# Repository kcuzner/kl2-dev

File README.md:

# Kinetis KL2 Development Board
### Kevin Cuzner

## Objective

Create a development board for a bare-metal ARM Microcontroller with minimal
parts while allowing for maximum prototypability.

## Purpose

To learn from hard experience what exactly is needed to implement from the
ground up a platform using an ARM-based microcontroller

## Idea

The board will have the following:

 * The Freescale MKL26Z32VFM4 48Mhz ARM Cortex-M0+ microcontroller, 32QFN (5mm)
 * Any needed support componenets
 * A DIP-compatible footprint. The goal is to be near the size of a teensy.

The goals are as follows:

 * $10 price point
    * $2.72 for the uC
    * $5 board
    * $3 supporting components
        * Perhaps a USB port even
 * Easy to construct with sufficient SMD soldering skill
 * We will produce 3 of them
    * 1 practice, 2 assembled on camera

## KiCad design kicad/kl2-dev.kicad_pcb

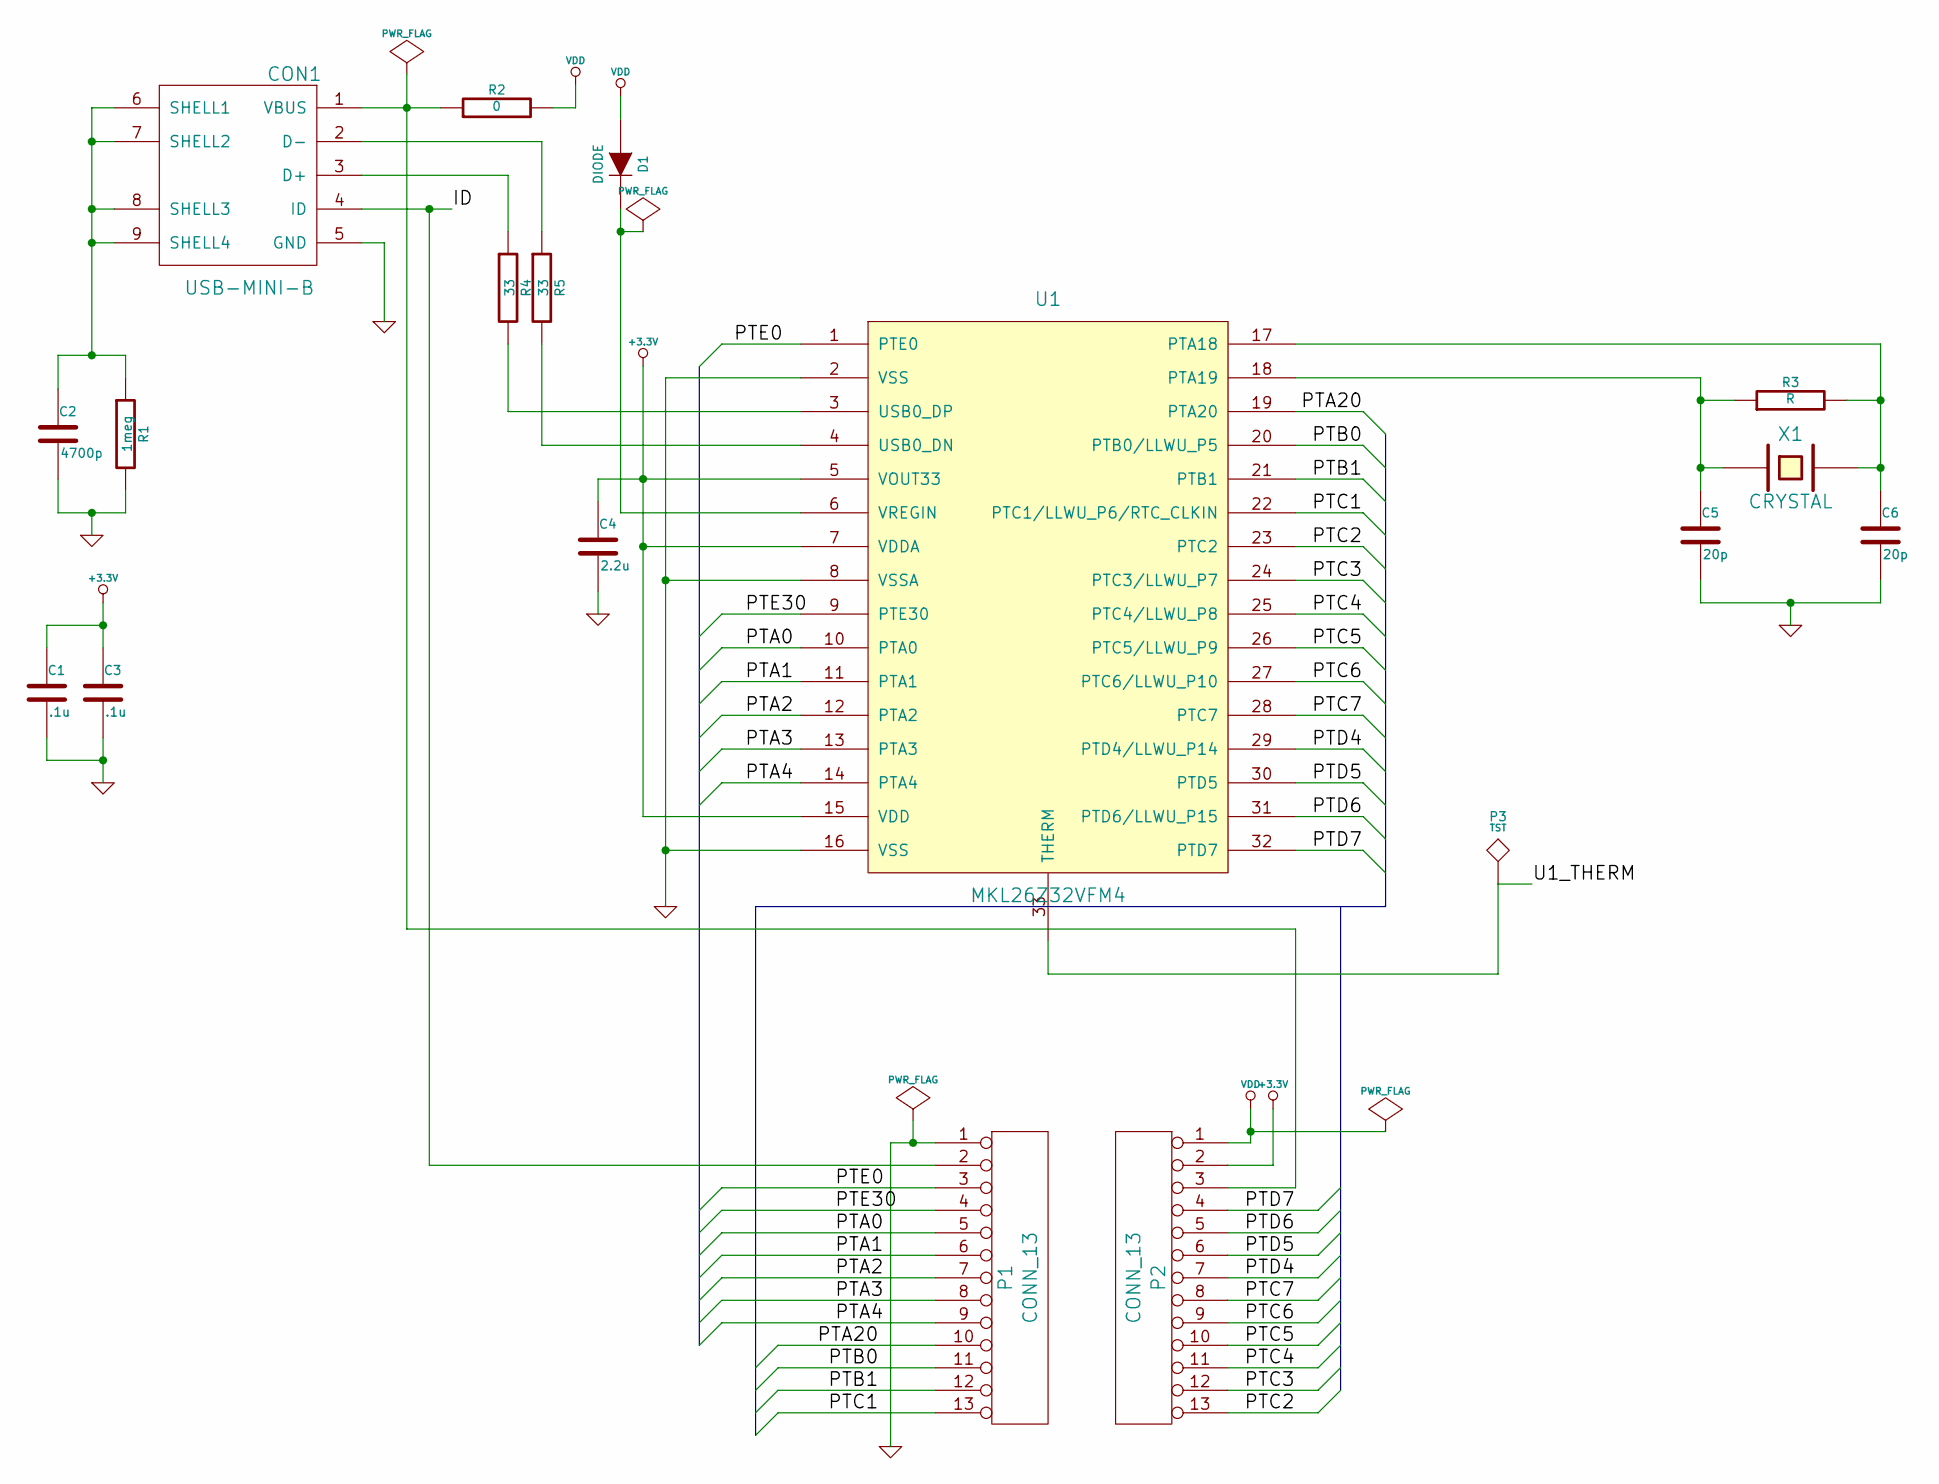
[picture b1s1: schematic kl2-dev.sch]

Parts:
C1, C3: .1u
C2: 4700p
C4: 2.2u
C5, C6: 20p
CON1: USB-MINI-B
D1: DIODE
P1, P2: CONN_13
P3: TST
R1: 1meg
R2: 0
R3: R
R4, R5: 33
U1: MKL26Z32VFM4
X1: CRYSTAL

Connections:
+3.3V: C1.1, C3.1, C4.1, P2.2, U1.5 (VOUT33), U1.7 (VDDA), U1.15 (VDD)
/ID: CON1.4 (ID), P1.2
/PTA0: P1.5, U1.10 (PTA0)
/PTA1: P1.6, U1.11 (PTA1)
/PTA2: P1.7, U1.12 (PTA2)
/PTA3: P1.8, U1.13 (PTA3)
/PTA4: P1.9, U1.14 (PTA4)
/PTA20: P1.10, U1.19 (PTA20)
/PTB0: P1.11, U1.20 (PTB0/LLWU_P5)
/PTB1: P1.12, U1.21 (PTB1)
/PTC1: P1.13, U1.22 (PTC1/LLWU_P6/RTC_CLKIN)
/PTC2: P2.13, U1.23 (PTC2)
/PTC3: P2.12, U1.24 (PTC3/LLWU_P7)
/PTC4: P2.11, U1.25 (PTC4/LLWU_P8)
/PTC5: P2.10, U1.26 (PTC5/LLWU_P9)
/PTC6: P2.9, U1.27 (PTC6/LLWU_P10)
/PTC7: P2.8, U1.28 (PTC7)
/PTD4: P2.7, U1.29 (PTD4/LLWU_P14)
/PTD5: P2.6, U1.30 (PTD5)
/PTD6: P2.5, U1.31 (PTD6/LLWU_P15)
/PTD7: P2.4, U1.32 (PTD7)
/PTE0: P1.3, U1.1 (PTE0)
/PTE30: P1.4, U1.9 (PTE30)
/U1_THERM: P3.1, U1.33 (THERM)
GND: C1.2, C2.2, C3.2, C4.2, C5.2, C6.2, CON1.5 (GND), P1.1, R1.2, U1.2 (VSS), U1.8 (VSSA), U1.16 (VSS)
unnamed: C5.1, R3.1, U1.18 (PTA19), X1.1
unnamed: C6.1, R3.2, U1.17 (PTA18), X1.2
unnamed: C2.1, CON1.6 (SHELL1), CON1.7 (SHELL2), CON1.8 (SHELL3), CON1.9 (SHELL4), R1.1
unnamed: D1.2 (K), U1.6 (VREGIN)
unnamed: R4.2, U1.3 (USB0_DP)
unnamed: CON1.3 (D+), R4.1
unnamed: R5.2, U1.4 (USB0_DN)
unnamed: CON1.2 (D-), R5.1
unnamed: CON1.1 (VBUS), P2.3, R2.1
VDD: D1.1 (A), P2.1, R2.2

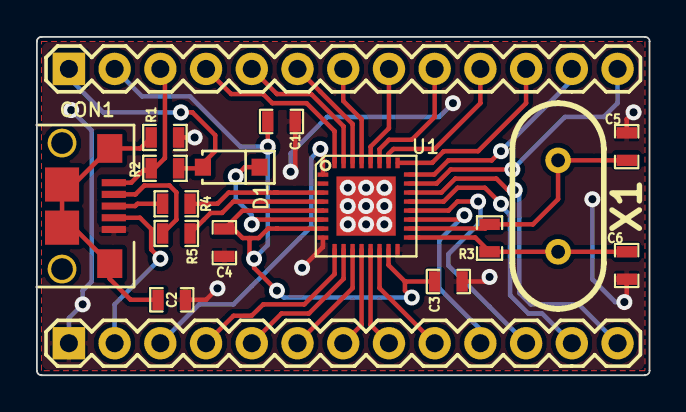
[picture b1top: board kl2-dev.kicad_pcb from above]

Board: 2 copper layers, 34.0 x 18.8 mm, 18 parts (1 on the bottom side), 35 nets.

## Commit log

2014-10-24 Created initial board with demonstration thermal pad
    We need pin 33 to be on its own special net because it shouldn't be
    connected. We also have not yet routed the flows.
2014-10-25 Finished routing all but gnd and thermal pad
2014-10-25 Added thermal pad and vias
2014-10-25 Fixed thermal pad to behave nicely with vias and finished fill
2014-10-25 Moved labels around to nice places and hid values
2014-10-25 Ignored gerber directory
2014-10-25 Fixed a small mistake in a bus on schematic
2014-10-25 Fixed oval holes to be large circles
    OSHPark didn't handle them very well
2014-10-25 Reduced thermal via size to minimum drill diameter
    TI has a paper about this and said to keep the via size <0.3mm (we can't quite
    get that small, but we can get close) and to have the spacing of thermal vias
    be about 1mm (we had this already by happenstance)
2014-10-25 Added usb resistors and fixed diode packaging
2015-01-19 Final schematic and pcb sent to fabricator
2015-01-19 Added family reference manual for KL26
    Next time, we find the family reference manual first...this microcontroller
    doesn't have an EzPort!
2015-01-19 Finally found a freaking header file
    This was located in the sample code for the Freedom Dev Platform for KL26 MCUs
    http://www.freescale.com/webapp/sps/site/prod_summary.jsp?code=FRDM-KL26Z&fpsp=1&tab=Design_Tools_Tab
2015-01-19 Split readme into log and added parts list spreadsheet
2015-01-19 Fixed typo in log
2015-01-19 Added initial build system with linker file
    Yay my first linker file created from a datasheet!
    The basis for this file was found in my teensy-oscilloscope repo:
    https://github.com/kcuzner/teensy-oscilloscope
2015-01-19 Added initial low-level startup code without interrupts
    This is based on the K20 code I have, but with some modifications since the
    Cortex-M0+ processor only supports a subset of the instruction set (I wish the
    compiler would output errors to that effect..instead it just gives back some
    nonsensical error)
2015-01-20 Added interrupt vector table and flash configuration
    Instead of doing the flash configuration with that sequential declaration thing
    that the K20 code had going, we assigned it specifically to live at 0x400. This
    should be much less error prone since screwing that up could possibly brick the
    chip permenently.
2015-01-20 Added initial common ARM Cortex-M0+ header and source
2015-01-20 Began adding shared bootloader region (overlayed)
    The bootloader will operate as a separate program, but with some restrictions:
    * It needs to live in RAM so that the entire flash can be accessed without
    modifying the bootloader code
    * It must be less than 4Kb in size, including variables (usb buffers as well)
    and stack
    The bootloader will basically function as follows:
2015-01-20 Created intial bootloader load-run-reset sequence
2015-01-20 Added interface for user programs to initiate the bootloader
2015-01-20 Fixed swapped src and dest in bootloader init
2015-01-20 Simplified linker script slightly & began adding usb driver for bootloader
2015-01-23 Added rudimentary usb handling functions and made linking safer
    There is now a restriction preventing .text from accessing .bootloader. This
    prevents any unintentional function calls. There is now a .bootstrap section
    which acts as the bridge between .bootloader and .text.
    We are also having memcpy issues...the additional union in usb_types.h seems
    to have stopped that for now, but it could come back.
2015-01-24 Added usb types to project file and ignored layout
2015-01-24 Moved main project into a bootloader folder
    We are going to go for the bootloader that lives in the first zone or two
    of the flash instead of the strange copying thing we have going now
2015-01-24 Split bootloader.c out into usb.c
2015-01-24 Renamed linker script and moved copy/clear functionality to C
    This is purely for portability. I would prefer to be able to reuse this code
    on a different processor (such as a Cortex-M4) without needing to fix the
    assembly again.
2015-02-02 Added CoreSight documentation and explanatory log entry
2016-12-13 Added blink firmware for an openocd test
2016-12-13 Made small changes to flash an LED. Success!
